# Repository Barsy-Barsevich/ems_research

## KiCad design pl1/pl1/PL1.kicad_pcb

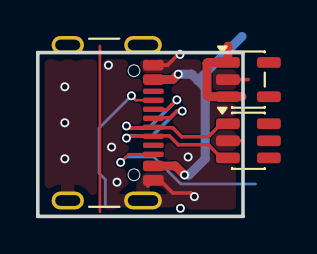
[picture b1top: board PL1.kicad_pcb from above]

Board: 4 copper layers, 11.4 x 9.1 mm, 3 parts (0 on the bottom side), 6 nets.

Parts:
J1: USB_C; USB_C_Receptacle_GCT_USB4105-xx-A_16P_TopMnt_Horizontal
U5: USBLC6-2SC6; SOT-23-6
U6: AP2112K-3.3; SOT-23-5

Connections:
/D+: J1.A6 (D+), J1.B6 (D+), U5.3 (I/O2)
/D-: J1.A7 (D-), J1.B7 (D-), U5.1 (I/O1)
GND: J1.A1 (GND), J1.A12 (GND), J1.B1 (GND), J1.B12 (GND), J1.S1 (SHIELD), U5.2 (GND), U6.2 (GND)
unnamed: U6.1 (VIN), U6.3 (EN)
unnamed: J1.A4 (VBUS), J1.A9 (VBUS), J1.B4 (VBUS), J1.B9 (VBUS)
VDD: U5.5 (VBUS), U6.5 (VOUT)
